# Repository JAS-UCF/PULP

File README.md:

# PULP

KiCAD project that contains a PCB layout, in hopes of over-optimizing the GNOR race

## Gameplan

implement a basic RP2040 board

- RP2040 processor *DONE*
- compass module *DONE*
- GPS module *DONE*
- PINOUT for I2C Bus 0 & 1 *DONE*
- PINOUT for PWM out Motor_Left & Motor_Right (2x3 Pins) *DONE*
- PINOUT for 3S Battery Power (External) ; Need to add regulator to help power the board *DONE*
- PINOUT for 6 GPIO pins *DONE*
- USB-C for programming and power *DONE*

## Questions?

Join the JAS Discord : <https://discord.gg/rzfwvgsg3Z>
Ask @ Peter about the project!

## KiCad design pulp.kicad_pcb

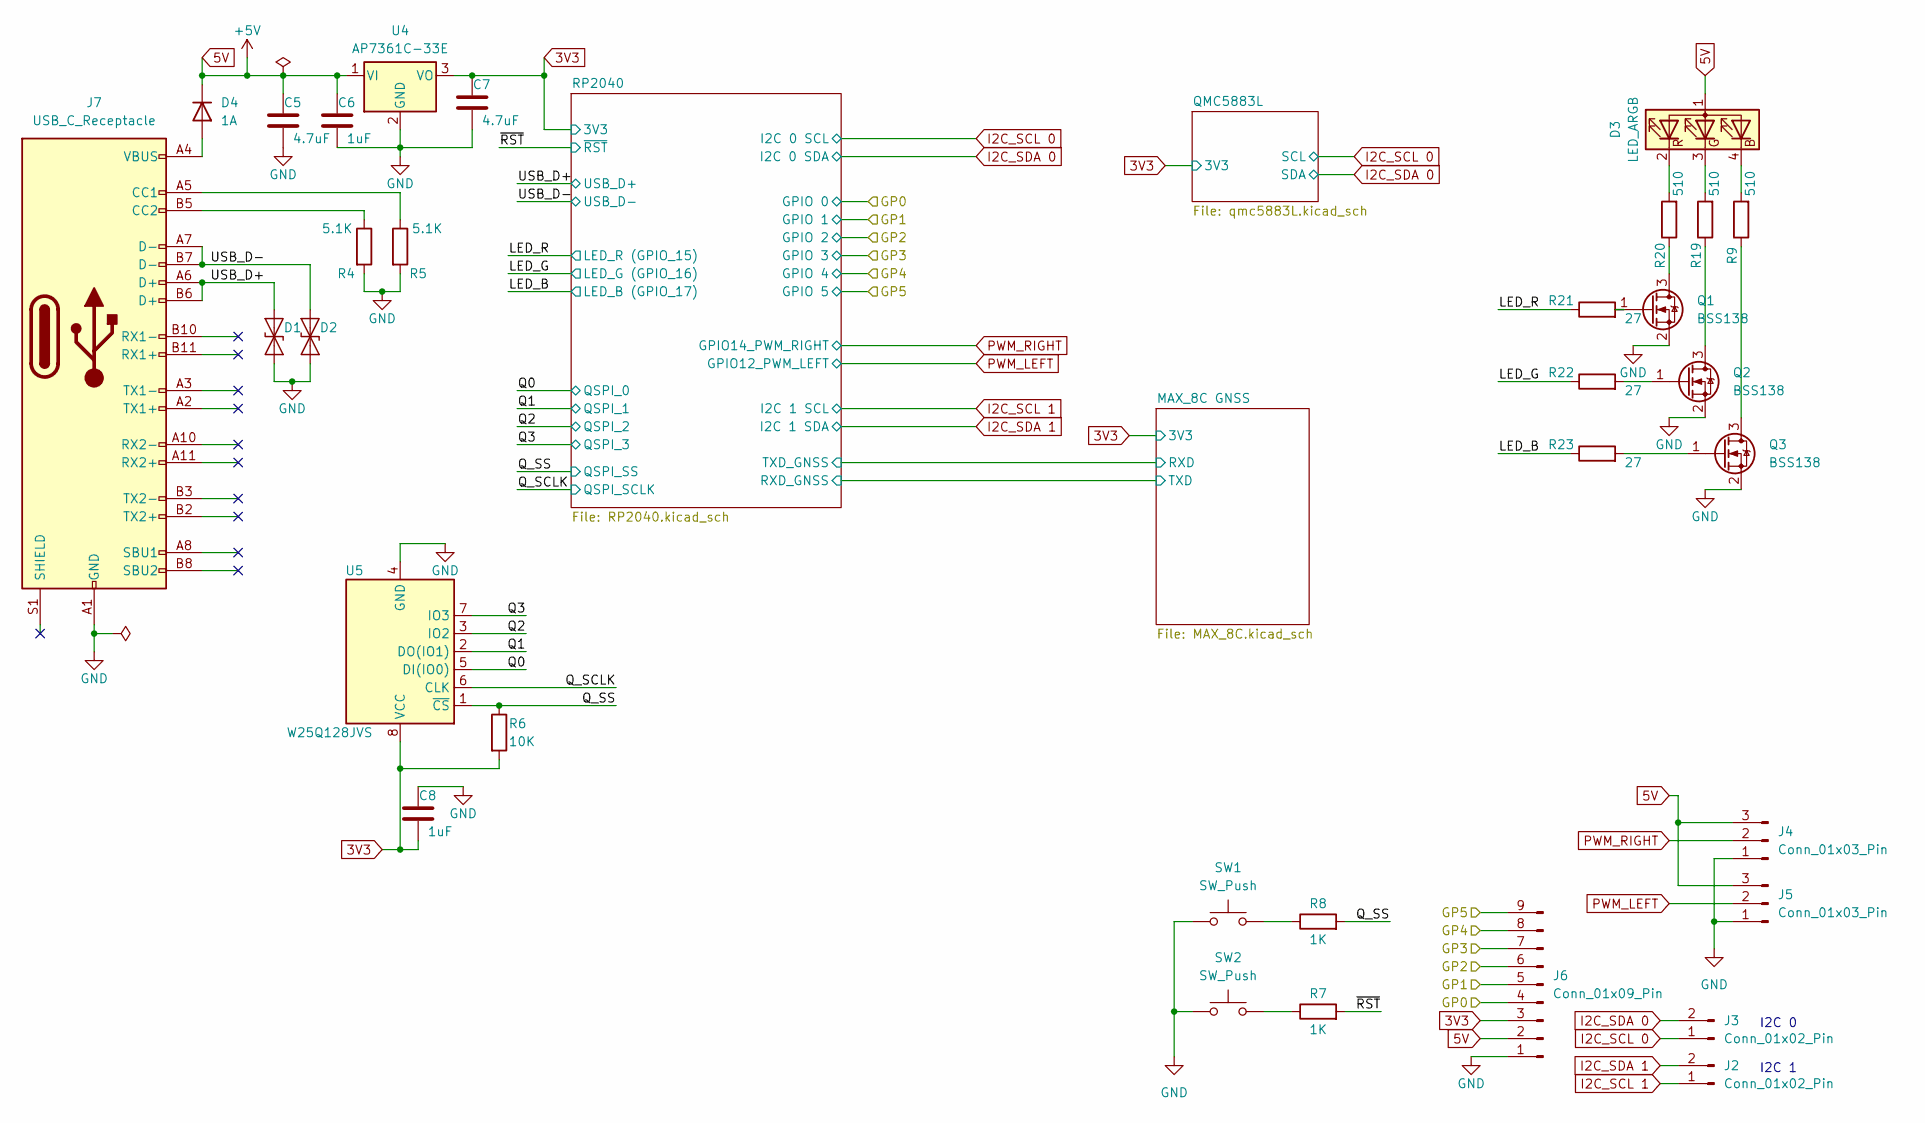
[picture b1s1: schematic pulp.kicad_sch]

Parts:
C5, C7: 4.7uF; C_0201_0603Metric
C6, C8: 1uF; C_0201_0603Metric
D1, D2: ESD9B5.0ST5G; D_SOD-923
D3: LED_ARGB; LED_RGB_1210
D4: 1A; D_1812_4532Metric
J2, J3: Conn_01x02_Pin; PinHeader_1x02_P2.54mm_Horizontal
J4, J5: Conn_01x03_Pin; PinHeader_1x03_P2.54mm_Horizontal
J6: Conn_01x09_Pin; PinHeader_1x09_P2.54mm_Vertical
J7: USB_C_Receptacle; USB_C_Receptacle_CNCTech_C-ARA1-AK51X
Q1, Q2, Q3: BSS138; SOT-23
R4, R5: 5.1K; R_0201_0603Metric
R6: 10K; R_0201_0603Metric
R7, R8: 1K; R_0201_0603Metric
R9, R19, R20: 510; R_0201_0603Metric
R21, R22, R23: 27; R_0201_0603Metric
SW1, SW2: SW_Push; SW_Push_SPST_NO_Alps_SKRK
U4: AP7361C-33E; SOT-223-3_TabPin2
U5: W25Q128JVS; SOIC-8_5.23x5.23mm_P1.27mm

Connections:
3V3: C7.1, C8.2, J6.3, R6.2, U4.3 (VO), U5.8 (VCC); also elsewhere on the board
5V: C5.1, C6.1, D3.1 (A), D4.1 (K), J4.3, J5.3, J6.2, U4.1 (VI)
/GP0: J6.4; also elsewhere on the board
/GP1: J6.5; also elsewhere on the board
/GP2: J6.6; also elsewhere on the board
/GP3: J6.7; also elsewhere on the board
/GP4: J6.8; also elsewhere on the board
/GP5: J6.9; also elsewhere on the board
/LED_B: R23.1; also elsewhere on the board
/LED_G: R22.1; also elsewhere on the board
/LED_R: R21.1; also elsewhere on the board
/Q0: U5.5 (DI(IO0)); also elsewhere on the board
/Q1: U5.2 (DO(IO1)); also elsewhere on the board
/Q2: U5.3 (IO2); also elsewhere on the board
/Q3: U5.7 (IO3); also elsewhere on the board
/Q_SCLK: U5.6 (CLK); also elsewhere on the board
/Q_SS: R6.1, R8.2, U5.1 (~CS); also elsewhere on the board
/USB_D+: D1.2 (A2), J7.A6 (D+), J7.B6 (D+); also elsewhere on the board
/USB_D-: D2.2 (A2), J7.A7 (D-), J7.B7 (D-); also elsewhere on the board
/~RST: R7.2; also elsewhere on the board
GND: C5.2, C6.2, C7.2, C8.1, D1.1 (A1), D2.1 (A1), J4.1, J5.1, J6.1, J7.A1 (GND), J7.A12 (GND), J7.B1 (GND), J7.B12 (GND), Q1.2 (S), Q2.2 (S), Q3.2 (S), R4.2, R5.2, SW1.1, SW2.1, U4.2 (GND), U5.4 (GND); also elsewhere on the board
I2C_SCL 0: J3.1; also elsewhere on the board
I2C_SCL 1: J2.1; also elsewhere on the board
I2C_SDA 0: J3.2; also elsewhere on the board
I2C_SDA 1: J2.2; also elsewhere on the board
unnamed: D3.4 (BK), R9.2
unnamed: D3.3 (GK), R19.2
unnamed: D3.2 (RK), R20.2
unnamed: D4.2 (A), J7.A4 (VBUS), J7.A9 (VBUS), J7.B4 (VBUS), J7.B9 (VBUS)
unnamed: J7.A5 (CC1), R5.1
unnamed: J7.B5 (CC2), R4.1
unnamed: Q1.3 (D), R20.1
unnamed: Q1.1 (G), R21.2
unnamed: Q2.3 (D), R19.1
unnamed: Q2.1 (G), R22.2
unnamed: Q3.3 (D), R9.1
unnamed: Q3.1 (G), R23.2
unnamed: R7.1, SW2.2
unnamed: R8.1, SW1.2
PWM_LEFT: J5.2; also elsewhere on the board
PWM_RIGHT: J4.2; also elsewhere on the board

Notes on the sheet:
I2C 0
I2C 1

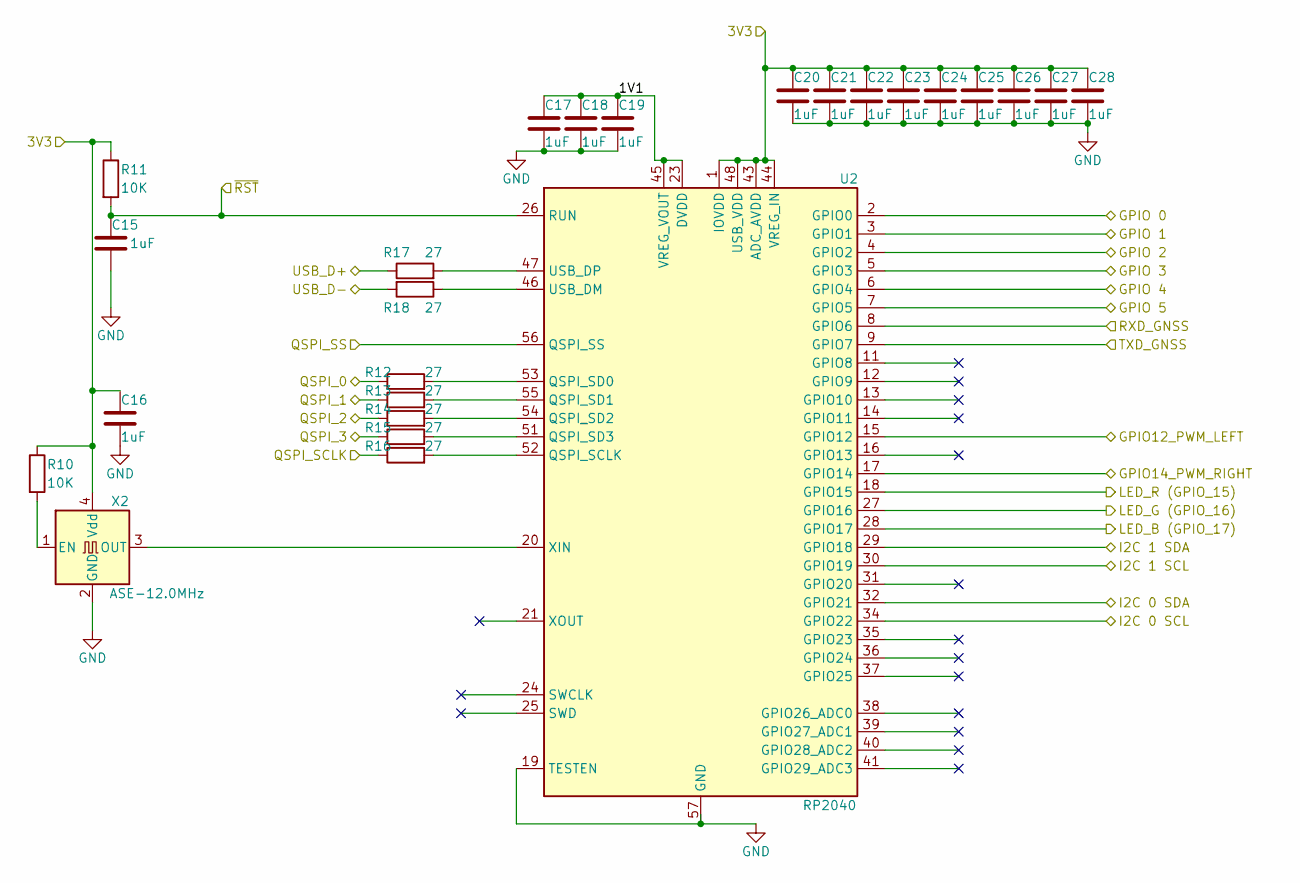
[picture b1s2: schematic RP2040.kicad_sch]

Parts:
C15, C16, C17, C18, C19, C20, C21, C22, C23, C24, C25, C26, C27, C28: 1uF; C_0201_0603Metric
R10, R11: 10K; R_0201_0603Metric
R12, R13, R14, R15, R16, R17, R18: 27; R_0201_0603Metric
U2: RP2040; QFN-56-1EP_7x7mm_P0.4mm_EP3.2x3.2mm
X2: ASE-12.0MHz; Oscillator_SMD_Abracon_ASE-4Pin_3.2x2.5mm

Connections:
3V3: C16.1, C20.1, C21.1, C22.1, C23.1, C24.1, C25.1, C26.1, C27.1, C28.1, R10.1, R11.1, U2.1 (IOVDD), U2.10 (IOVDD), U2.22 (IOVDD), U2.33 (IOVDD), U2.42 (IOVDD), U2.43 (ADC_AVDD), U2.44 (VREG_IN), U2.48 (USB_VDD), U2.49 (IOVDD), X2.4 (Vdd); also elsewhere on the board
/GP0: U2.2 (GPIO0); also elsewhere on the board
/GP1: U2.3 (GPIO1); also elsewhere on the board
/GP2: U2.4 (GPIO2); also elsewhere on the board
/GP3: U2.5 (GPIO3); also elsewhere on the board
/GP4: U2.6 (GPIO4); also elsewhere on the board
/GP5: U2.7 (GPIO5); also elsewhere on the board
/LED_B: U2.28 (GPIO17); also elsewhere on the board
/LED_G: U2.27 (GPIO16); also elsewhere on the board
/LED_R: U2.18 (GPIO15); also elsewhere on the board
/MAX_8C GNSS/RXD: U2.9 (GPIO7); also elsewhere on the board
/MAX_8C GNSS/TXD: U2.8 (GPIO6); also elsewhere on the board
/Q0: R12.1; also elsewhere on the board
/Q1: R13.1; also elsewhere on the board
/Q2: R14.1; also elsewhere on the board
/Q3: R15.1; also elsewhere on the board
/Q_SCLK: R16.1; also elsewhere on the board
/Q_SS: U2.56 (QSPI_SS); also elsewhere on the board
/RP2040/1V1: C17.1, C18.1, C19.1, U2.23 (DVDD), U2.45 (VREG_VOUT), U2.50 (DVDD)
/USB_D+: R17.1; also elsewhere on the board
/USB_D-: R18.2; also elsewhere on the board
/~RST: C15.1, R11.2, U2.26 (RUN); also elsewhere on the board
GND: C15.2, C16.2, C17.2, C18.2, C19.2, C20.2, C21.2, C22.2, C23.2, C24.2, C25.2, C26.2, C27.2, C28.2, U2.19 (TESTEN), U2.57 (GND), X2.2 (GND); also elsewhere on the board
I2C_SCL 0: U2.34 (GPIO22); also elsewhere on the board
I2C_SCL 1: U2.30 (GPIO19); also elsewhere on the board
I2C_SDA 0: U2.32 (GPIO21); also elsewhere on the board
I2C_SDA 1: U2.29 (GPIO18); also elsewhere on the board
unnamed: R16.2, U2.52 (QSPI_SCLK)
unnamed: R12.2, U2.53 (QSPI_SD0)
unnamed: R13.2, U2.55 (QSPI_SD1)
unnamed: R14.2, U2.54 (QSPI_SD2)
unnamed: R15.2, U2.51 (QSPI_SD3)
unnamed: R18.1, U2.46 (USB_DM)
unnamed: R17.2, U2.47 (USB_DP)
unnamed: U2.20 (XIN), X2.3 (OUT)
unnamed: R10.2, X2.1 (EN)
PWM_LEFT: U2.15 (GPIO12); also elsewhere on the board
PWM_RIGHT: U2.17 (GPIO14); also elsewhere on the board

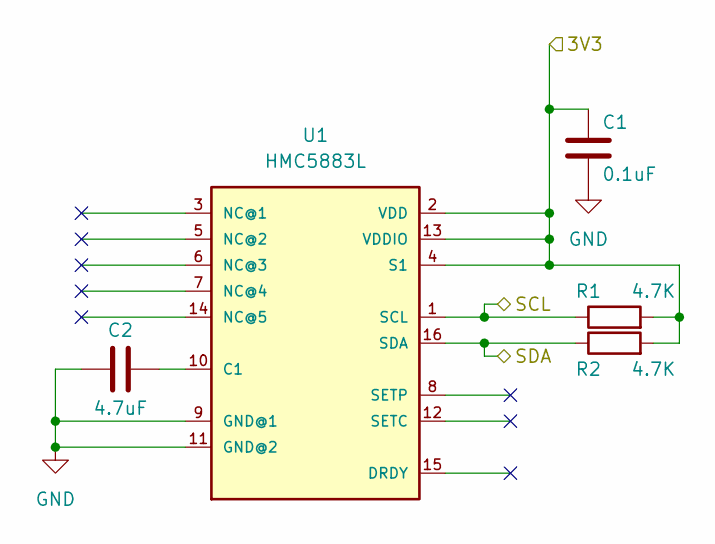
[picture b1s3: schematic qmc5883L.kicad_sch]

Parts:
C1: 0.1uF; C_0201_0603Metric
C2: 4.7uF; C_0201_0603Metric
R1, R2: 4.7K; R_0201_0603Metric
U1: HMC5883L

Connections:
3V3: C1.1, R1.2, R2.2, U1.2 (VDD), U1.4 (S1), U1.13 (VDDIO); also elsewhere on the board
GND: C1.2, C2.1, U1.9 (GND@1), U1.11 (GND@2); also elsewhere on the board
I2C_SCL 0: R1.1, U1.1 (SCL); also elsewhere on the board
I2C_SDA 0: R2.1, U1.16 (SDA); also elsewhere on the board
unnamed: C2.2, U1.10 (C1)

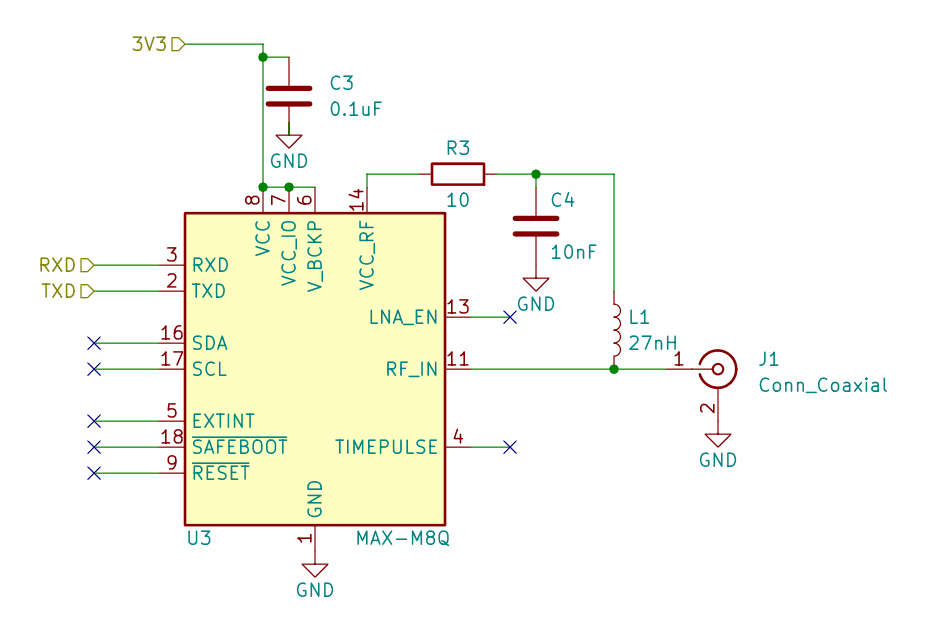
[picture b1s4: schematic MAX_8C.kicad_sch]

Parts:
C3: 0.1uF; C_0201_0603Metric
C4: 10nF; C_0201_0603Metric
J1: Conn_Coaxial; U.FL_Molex_MCRF_73412-0110_Vertical
L1: 27nH; L_0201_0603Metric
R3: 10; R_0201_0603Metric
U3: MAX-M8Q; ublox_MAX

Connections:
3V3: C3.1, U3.6 (V_BCKP), U3.7 (VCC_IO), U3.8 (VCC); also elsewhere on the board
/MAX_8C GNSS/RXD: U3.3 (RXD); also elsewhere on the board
/MAX_8C GNSS/TXD: U3.2 (TXD); also elsewhere on the board
GND: C3.2, C4.2, J1.2 (Ext), U3.1 (GND), U3.10 (GND), U3.12 (GND); also elsewhere on the board
unnamed: C4.1, L1.1, R3.2
unnamed: J1.1 (In), L1.2, U3.11 (RF_IN)
unnamed: R3.1, U3.14 (VCC_RF)

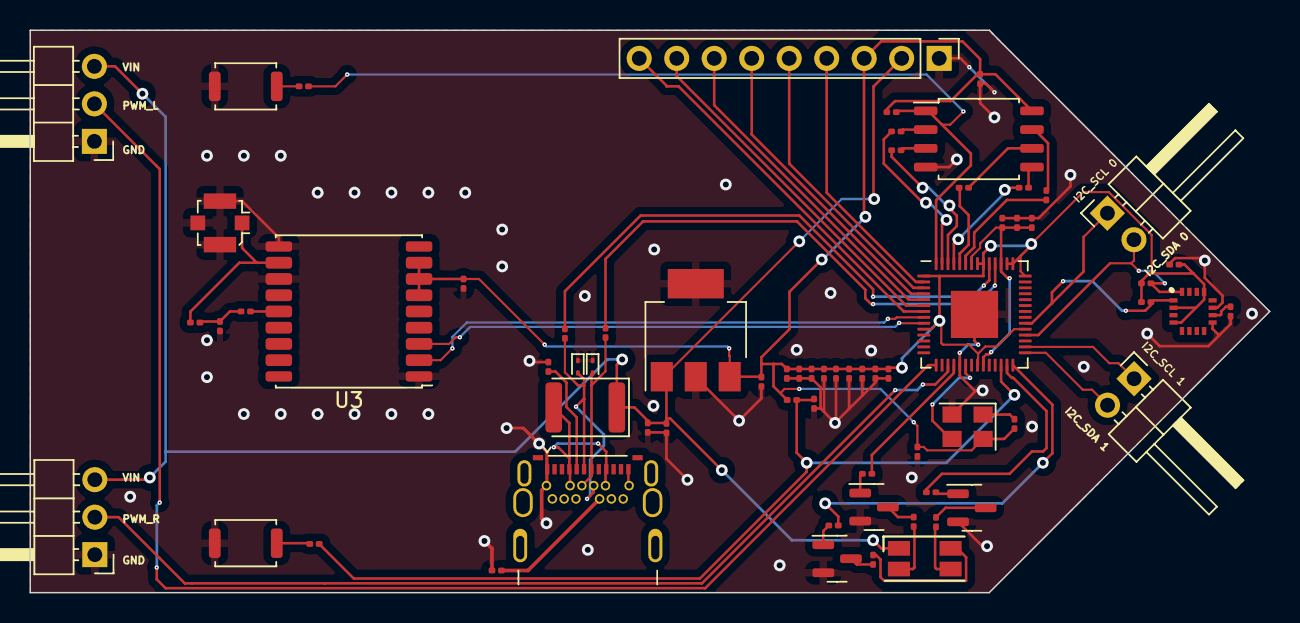
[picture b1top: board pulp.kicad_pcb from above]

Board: 2 copper layers, 84.0 x 38.1 mm, 68 parts (0 on the bottom side), 57 nets.

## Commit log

2024-03-23 update text
2024-03-23 pulp beginnings using RP2040
2024-03-23 exposes proper GPIO
2024-03-23 jas discord link
2024-03-23 remove BS license
2024-03-23 switching to a more sane lisence
2024-03-23 remove cc
2024-03-23 final save of day 1
2024-03-23 adds 2 new PWM PINS for the Motors
2024-03-23 refine project scope
2024-03-23 started PCB layout
2024-03-24 made edits to PWM
2024-03-24 adds QMC5883L
2024-03-25 adds GNSS module
2024-03-25 remove lock file
2024-03-25 dont commit lock files
2024-03-25 finalized a lot of sub-modules
2024-03-25 NO ERC ERRORS!!!!
2024-03-25 clean up backups and saves
2024-03-25 Finalized voltage regulator for Battery
2024-03-25 spelling
2024-03-26 begins PCB routing for the final design V1
2024-03-26 edits to pcb board
2024-03-30 finished pcb layout
2024-04-02 agged ground VIA to help remove island
